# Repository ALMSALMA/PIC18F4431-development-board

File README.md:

# PIC18F4431-development-board

In this project, PIC 18F4431 developement board's schematic and PCB were designed using EAGLE. For more information see **Staj-1** repository.

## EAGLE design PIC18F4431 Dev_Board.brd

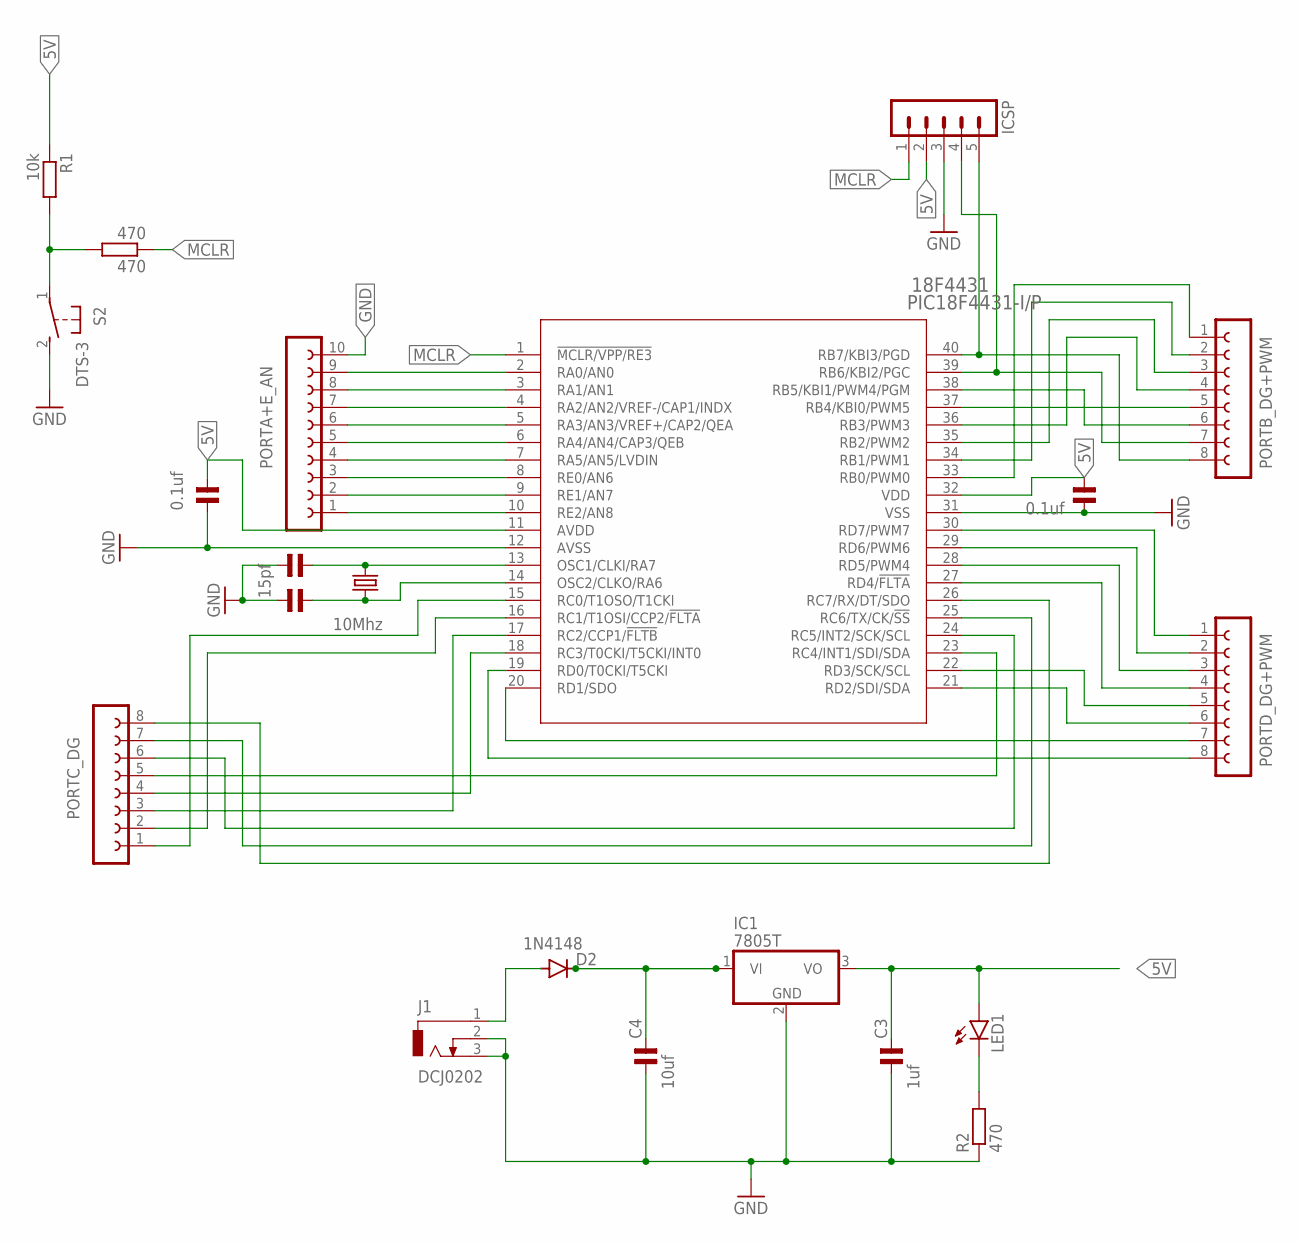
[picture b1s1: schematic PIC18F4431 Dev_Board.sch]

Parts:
18F4431: PIC18F4431-I/P; PDIP40_600MC
470: 470; 0207/10
C1, C2: 15pf; ENP1,5-4
C3: 1uf; ENP1,5-4
C4: 10uf; ENP1,5-4
C5, C6: 0.1uf; ENP1,5-4
D2: 1N4148; DO35-7
IC1: 7805T; TO220H
ICSP: MA05-1
J1: DCJ0202
LED1: LED5MM
PORTA+E_AN: FE10-1; FE10
PORTB_DG+PWM: FE08-1; FE08
PORTC_DG: FE08-1; FE08
PORTD_DG+PWM: FE08-1; FE08
Q2: 10Mhz; HC49/S
R1: 10k; 0207/10
R2: 470; 0207/10
S2: DTS-3

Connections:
5V: 18F4431.11 (AVDD), 18F4431.32 (VDD), C3.2, C5.2, C6.2, IC1.3 (VO), ICSP.2, LED1.A, R1.1
GND: 18F4431.12 (AVSS), 18F4431.31 (VSS), C1.1, C2.1, C3.1, C4.1, C5.1, C6.1, IC1.2 (GND), ICSP.3, J1.2, J1.3, PORTA+E_AN.10, R2.1, S2.2
MCLR: 18F4431.1 (!MCLR/VPP/RE3), 470.1, ICSP.1
unnamed: 18F4431.14 (OSC2/CLKO/RA6), C2.2, Q2.1
unnamed: 18F4431.13 (OSC1/CLKI/RA7), C1.2, Q2.2
unnamed: D2.A, J1.1
unnamed: LED1.K (C), R2.2
unnamed: 18F4431.15 (RC0/T1OSO/T1CKI), PORTC_DG.1
unnamed: 18F4431.40 (RB7/KBI3/PGD), ICSP.5, PORTB_DG+PWM.8
unnamed: 18F4431.39 (RB6/KBI2/PGC), ICSP.4, PORTB_DG+PWM.7
unnamed: C4.2, D2.C, IC1.1 (VI)
unnamed: 470.2, R1.2, S2.1
unnamed: 18F4431.38 (RB5/KBI1/PWM4/PGM), PORTB_DG+PWM.6
unnamed: 18F4431.37 (RB4/KBI0/PWM5), PORTB_DG+PWM.5
unnamed: 18F4431.36 (RB3/PWM3), PORTB_DG+PWM.4
unnamed: 18F4431.35 (RB2/PWM2), PORTB_DG+PWM.3
unnamed: 18F4431.34 (RB1/PWM1), PORTB_DG+PWM.2
unnamed: 18F4431.33 (RB0/PWM0), PORTB_DG+PWM.1
unnamed: 18F4431.30 (RD7/PWM7), PORTD_DG+PWM.1
unnamed: 18F4431.29 (RD6/PWM6), PORTD_DG+PWM.2
unnamed: 18F4431.28 (RD5/PWM4), PORTD_DG+PWM.3
unnamed: 18F4431.27 (RD4/!FLTA), PORTD_DG+PWM.4
unnamed: 18F4431.22 (RD3/SCK/SCL), PORTD_DG+PWM.5
unnamed: 18F4431.21 (RD2/SDI/SDA), PORTD_DG+PWM.6
unnamed: 18F4431.20 (RD1/SDO), PORTD_DG+PWM.7
unnamed: 18F4431.19 (RD0/T0CKI/T5CKI), PORTD_DG+PWM.8
unnamed: 18F4431.2 (RA0/AN0), PORTA+E_AN.9
unnamed: 18F4431.3 (RA1/AN1), PORTA+E_AN.8
unnamed: 18F4431.4 (RA2/AN2/VREF-/CAP1/INDX), PORTA+E_AN.7
unnamed: 18F4431.5 (RA3/AN3/VREF+/CAP2/QEA), PORTA+E_AN.6
unnamed: 18F4431.6 (RA4/AN4/CAP3/QEB), PORTA+E_AN.5
unnamed: 18F4431.7 (RA5/AN5/LVDIN), PORTA+E_AN.4
unnamed: 18F4431.8 (RE0/AN6), PORTA+E_AN.3
unnamed: 18F4431.9 (RE1/AN7), PORTA+E_AN.2
unnamed: 18F4431.10 (RE2/AN8), PORTA+E_AN.1
unnamed: 18F4431.16 (RC1/T1OSI/CCP2/!FLTA), PORTC_DG.2
unnamed: 18F4431.17 (RC2/CCP1/!FLTB), PORTC_DG.3
unnamed: 18F4431.18 (RC3/T0CKI/T5CKI/INT0), PORTC_DG.4
unnamed: 18F4431.23 (RC4/INT1/SDI/SDA), PORTC_DG.5
unnamed: 18F4431.24 (RC5/INT2/SCK/SCL), PORTC_DG.6
unnamed: 18F4431.25 (RC6/TX/CK/!SS), PORTC_DG.7
unnamed: 18F4431.26 (RC7/RX/DT/SDO), PORTC_DG.8

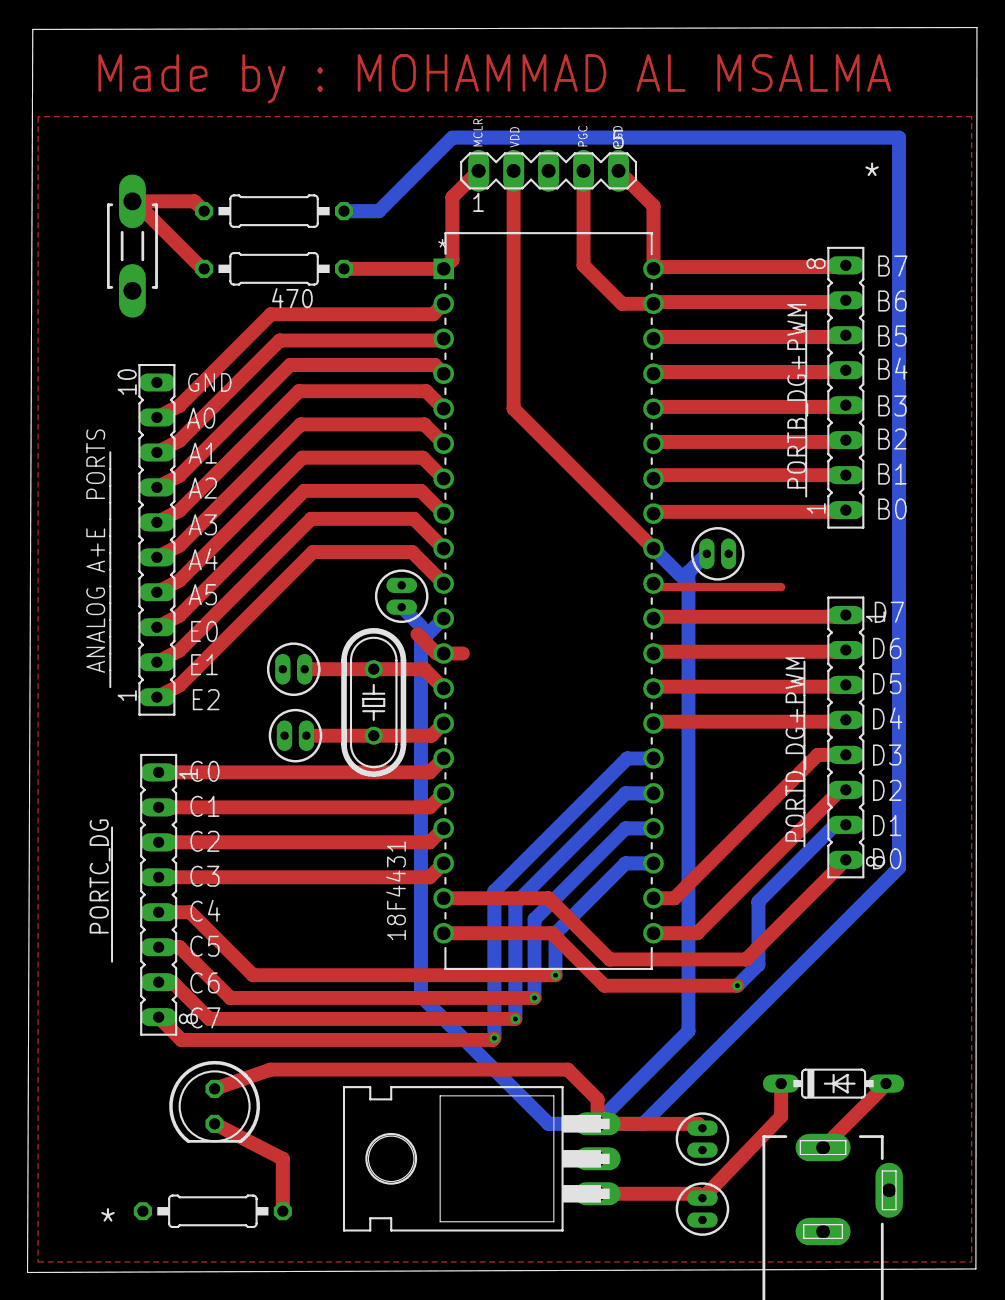
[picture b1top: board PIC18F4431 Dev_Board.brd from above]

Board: 2 copper layers, 69.0 x 90.4 mm, 21 parts (0 on the bottom side), 42 nets.

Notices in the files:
parts and their libraries:
cap-pan40: Copyright (C) 2004, Bob Starr
